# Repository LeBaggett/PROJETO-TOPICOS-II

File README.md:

# Videogame Portátil com STM32F103 (Blue Pill)

## Sumário
- [1. Introdução](#1-introdução)
- [2. Objetivos do Projeto](#2-objetivos-do-projeto)
  - [2.1 Objetivo Geral](#21-objetivo-geral)
  - [2.2 Objetivos Específicos](#22-objetivos-específicos)
- [3. Visão Geral do Sistema](#3-visão-geral-do-sistema)
  - [3.1 Arquitetura Geral](#31-arquitetura-geral)
  - [3.2 Fluxo Geral de Operação](#32-fluxo-geral-de-operação)
- [4. Escolha dos Componentes](#4-escolha-dos-componentes)
  - [4.1 Microcontrolador – STM32F103C8T6 (Blue Pill)](#41-microcontrolador--stm32f103c8t6-blue-pill)
  - [4.2 Display – Nokia 5110 (PCD8544)](#42-display--nokia-5110-pcd8544)
  - [4.3 Armazenamento – Cartão SD (Modo SPI)](#43-armazenamento--cartão-sd-modo-spi)
  - [4.4 Interface de Entrada – Botões Táteis](#44-interface-de-entrada--botões-táteis)
  - [4.5 Áudio – Buzzer Passivo](#45-áudio--buzzer-passivo)
- [5. Projeto do Esquemático](#5-projeto-do-esquemático)
  - [5.1 Circuito de Alimentação](#51-circuito-de-alimentação)
  - [5.2 Desacoplamento do Microcontrolador e Periféricos](#52-desacoplamento-do-microcontrolador-e-periféricos)
  - [5.3 Comunicação SPI](#53-comunicação-spi)
  - [5.4 Interface com o Display](#54-interface-com-o-display)
  - [5.5 Interface com o Cartão SD](#55-interface-com-o-cartão-sd)
  - [5.6 Interface de Entrada (Botões)](#56-interface-de-entrada-botões)
  - [5.7 Circuito de Áudio](#57-circuito-de-áudio)
- [6. Definição de Pinout](#6-definição-de-pinout)
  - [6.1 Tabela de Pinout](#61-tabela-de-pinout)
  - [6.2 Justificativa do Pinout](#62-justificativa-do-pinout)
- [7. Projeto da PCB](#7-projeto-da-pcb)
  - [7.1 Considerações Gerais](#71-considerações-gerais)
  - [7.2 Primeira Versão da PCB](#72-primeira-versão-da-pcb)
  - [7.3 Segunda Versão da PCB](#73-segunda-versão-da-pcb)
  - [7.4 Análise do Layout Final](#74-análise-do-layout-final)
- [8. Visualização 3D e Montagem](#8-visualização-3d-e-montagem)
  - [8.1 Modelo 3D da PCB](#81-modelo-3d-da-pcb)
  - [8.2 Considerações de Montagem](#82-considerações-de-montagem)
- [9. Conclusão](#9-conclusão)
- [10. Referências](#10-referências)

---

## 1. Introdução
Este documento apresenta a **documentação técnica do hardware** de um videogame portátil desenvolvido com foco educacional e experimental, baseado no microcontrolador **STM32F103C8T6 (Blue Pill)**. O objetivo principal desta documentação é **descrever, justificar e analisar as decisões de projeto de hardware**, desde a escolha dos componentes até o esquemático elétrico e o layout final da PCB.

O projeto foi concebido para integrar conceitos de eletrônica digital, sistemas embarcados e boas práticas de projeto de placas de circuito impresso, priorizando simplicidade, modularidade e confiabilidade elétrica. Questões relacionadas a firmware são abordadas apenas quando necessárias para justificar decisões de hardware.

---

## 2. Objetivos do Projeto

### 2.1 Objetivo Geral
Desenvolver e documentar o **hardware de um videogame portátil**, incluindo esquemático elétrico e PCB, utilizando componentes amplamente disponíveis e de baixo custo, garantindo funcionamento estável e possibilidade de expansão futura.

### 2.2 Objetivos Específicos
- Selecionar um microcontrolador adequado para aplicações gráficas simples e controle de periféricos  
- Projetar um circuito de alimentação estável em 3,3 V  
- Implementar comunicação SPI confiável para display gráfico e cartão SD  
- Desenvolver uma interface física com botões e sinalização sonora  
- Aplicar boas práticas de desacoplamento, filtragem e layout de PCB  

---

## 3. Visão Geral do Sistema

### 3.1 Arquitetura Geral
O sistema é composto pelos seguintes blocos funcionais:
- Unidade de processamento baseada no STM32F103  
- Interface de usuário composta por display gráfico, botões e buzzer  
- Sistema de armazenamento removível via cartão SD  
- Circuito de alimentação em 3,3 V  

### 3.2 Fluxo Geral de Operação
1. Energização do circuito e estabilização da alimentação  
2. Inicialização do microcontrolador  
3. Configuração dos periféricos SPI  
4. Leitura das entradas do usuário  
5. Atualização do display e geração de áudio  

---

## 4. Escolha dos Componentes

### 4.1 Microcontrolador – STM32F103C8T6 (Blue Pill)
<div align="center">
<br><figure align="center">
  <div> 

  </div>
</figure><br>
<div align="center">
  <figcaption>
    <b>Figura 1</b> – Microcontrolador STM32F103C8T6 e sua Dev Board (Blue Pill)
  </figcaption>
</div><br>
</div>

O STM32F103C8T6 foi escolhido por oferecer um equilíbrio adequado entre desempenho, custo e disponibilidade. O núcleo ARM Cortex-M3 operando a até 72 MHz é suficiente para aplicações gráficas simples, leitura de entradas e controle de periféricos.

A utilização do módulo Blue Pill reduz a complexidade do projeto, facilita testes e depuração e permite foco no desenvolvimento do restante do hardware.

## Visão Geral

A família **STM32F103xx de média densidade da linha performance** incorpora o núcleo **Arm® Cortex®-M3 de 32 bits**, de alto desempenho, operando a uma frequência de até **72 MHz**, memórias embarcadas de alta velocidade (**Flash de até 128 Kbytes** e **SRAM de até 20 Kbytes**), além de uma ampla variedade de **E/S aprimoradas** e **periféricos** conectados a dois barramentos **APB**.

Todos os dispositivos oferecem **dois ADCs de 12 bits**, **três temporizadores de uso geral de 16 bits** mais **um temporizador PWM**, bem como interfaces de comunicação padrão e avançadas: até **dois I2Cs e SPIs**, **três USARTs**, **USB** e **CAN**.

Os dispositivos operam com alimentação de **2,0 a 3,6 V**. Estão disponíveis tanto na faixa de temperatura de **–40 a +85 °C** quanto na faixa estendida de **–40 a +105 °C**. Um conjunto abrangente de **modos de economia de energia** permite o projeto de aplicações de baixo consumo.

A família STM32F103xx de média densidade inclui dispositivos em **seis tipos diferentes de encapsulamento**, variando de **36 pinos a 100 pinos**. Dependendo do dispositivo escolhido, diferentes conjuntos de periféricos são incluídos. A descrição a seguir fornece uma visão geral da gama completa de periféricos oferecidos por esta família.

Essas características tornam a família de microcontroladores STM32F103xx de média densidade adequada para uma ampla gama de aplicações, como **acionamento de motores**, **controle de aplicações**, **equipamentos médicos e portáteis**, **periféricos para PC e jogos**, **plataformas GPS**, **aplicações industriais**, **CLPs**, **inversores**, **impressoras**, **scanners**, **sistemas de alarme**, **interfones de vídeo** e **sistemas HVAC**.

---

## Características

### Núcleo
- Núcleo **Arm® Cortex®-M3 de 32 bits**
- Frequência máxima de **72 MHz**
- Desempenho de **1,25 DMIPS/MHz** (Dhrystone 2.1) com acesso à memória sem wait states
- Multiplicação em ciclo único e divisão por hardware

### Memórias
- **64 ou 128 Kbytes** de memória Flash
- **20 Kbytes** de SRAM

### Gerenciamento de clock, reset e alimentação
- Alimentação da aplicação e E/S de **2,0 a 3,6 V**
- **POR**, **PDR** e detector de tensão programável (**PVD**)
- Oscilador a cristal de **4 a 16 MHz**
- Oscilador RC interno de **8 MHz** calibrado em fábrica
- Oscilador RC interno de **40 kHz**
- **PLL** para clock da CPU
- Oscilador de **32 kHz** para RTC com calibração

### Baixo consumo
- Modos **Sleep**, **Stop** e **Standby**
- Alimentação **VBAT** para RTC e registradores de backup

### Conversores A/D
- **2 conversores A/D de 12 bits**, **1 µs** (até **16 canais**)
- Faixa de conversão: **0 a 3,6 V**
- Capacidade de **dupla amostragem e retenção**
- **Sensor de temperatura** interno

### DMA
- Controlador DMA de **7 canais**
- Periféricos suportados: temporizadores, ADC, SPI, I2C e USART

### Portas de E/S
- Até **80 portas de E/S rápidas**
- **26 / 37 / 51 / 80 E/S**, todas mapeáveis em **16 vetores de interrupção externa** e quase todas **tolerantes a 5 V**

### Depuração
- Interfaces de depuração **Serial Wire Debug (SWD)** e **JTAG**

### Temporizadores
- **Três temporizadores de 16 bits**, cada um com até 4 canais IC/OC/PWM ou contador de pulsos e entrada de encoder incremental (quadratura)
- Temporizador PWM de **16 bits para controle de motores**, com geração de dead-time e parada de emergência
- **Dois watchdogs** (independente e de janela)
- Temporizador **SysTick** de 24 bits (contador regressivo)

### Interfaces de comunicação
- Até **nove interfaces de comunicação**
- Até **duas interfaces I2C** (SMBus/PMBus®)
- Até **três USARTs** (interface ISO 7816, LIN, capacidade IrDA, controle de modem)
- Até **duas interfaces SPI** (até **18 Mbit/s**)
- Interface **CAN 2.0B Active**
- Interface **USB 2.0 Full-Speed**

### Outros recursos
- Unidade de cálculo **CRC**
- **ID único de 96 bits**
- Encapsulamentos **ECOPACK®**

### 4.2 Display – Nokia 5110 (PCD8544)

<br><div align="center">
  <figure>
      
  </figure><br>
</div><br>

<div align="center">
  <figcaption>
    <b>Figura 2</b> – Display LCD Nokia 5110
  </figcaption>
</div><br>

O display Nokia 5110 foi selecionado por sua simplicidade de interface, baixo consumo de energia e ampla documentação disponível. Sua resolução de 84x48 pixels é adequada para jogos 2D simples e menus gráficos.

### 4.3 Armazenamento – Cartão SD (Modo SPI)

<br><div align="center">
  <figure>
      
  </figure><br>
</div><br>

<div align="center">
  <figcaption>
    <b>Figura 3</b> – Módulo Micro Cartão SD
  </figcaption>
</div><br>

O cartão SD operando em modo SPI oferece alta capacidade de armazenamento com baixa complexidade de hardware. Ele é utilizado para armazenamento de dados persistentes como estados de jogos e configurações.

### 4.4 Interface de Entrada – Botões Táteis
Os botões táteis foram escolhidos por sua robustez, simplicidade elétrica e fácil integração com GPIOs do microcontrolador. O tratamento de debounce é realizado via software.

### 4.5 Áudio – Buzzer Passivo
O buzzer passivo permite geração de áudio por PWM, utilizando timers internos do STM32. Essa abordagem oferece flexibilidade sonora com baixo custo e simplicidade de hardware.

---

## 5. Projeto do Esquemático

O esquemático elétrico do videogame portátil foi desenvolvido com foco em simplicidade, robustez elétrica e boas práticas de projeto para sistemas embarcados. A organização do circuito segue uma divisão funcional clara, permitindo fácil compreensão, manutenção e futuras modificações.

<div align="center">
<figure align="center">
  
  <figcaption>
    <b>Figura 4</b> – Esquemático elétrico versão v1
  </figcaption>
</figure>
</div><br>

<p align="center">
  <a href="hardware/ProtoGame/ProtoGame-jobset-file/ProtoGame-schematic-v1/ProtoGame.pdf">Esquemático elétrico completo (PDF)</a>
</p><br>

---

### 5.1 Circuito de Alimentação

O sistema foi projetado para operar integralmente em **3,3 V**, tensão compatível com o microcontrolador STM32F103C8T6 e com todos os periféricos utilizados. A alimentação principal é fornecida por uma bateria, cuja tensão é regulada por um regulador linear **AMS1117-3.3**.

O regulador AMS1117 foi escolhido por sua ampla disponibilidade e facilidade de aplicação, sendo adequado para projetos educacionais e protótipos funcionais. Apesar de sua eficiência inferior quando comparado a reguladores chaveados, seu uso é justificado pelo consumo moderado do sistema e pela simplicidade do circuito.

Na entrada e na saída do regulador são utilizados capacitores de filtragem, conforme recomendado pelo fabricante, garantindo estabilidade da tensão e evitando oscilações indesejadas.

---

### 5.2 Capacitores Bulk e Filtragem de Baixa Frequência

O capacitor **bulk** de maior valor (47 µF) foi inserido na linha de alimentação principal com o objetivo de absorver variações lentas de corrente e fornecer energia instantânea durante picos de consumo, especialmente durante inicialização do sistema e acesso ao cartão SD.

Além do capacitor bulk principal, capacitores adicionais de **4,7 µF** são distribuídos próximos a blocos específicos do circuito, atuando como suporte local de energia. Essa abordagem reduz quedas momentâneas de tensão e melhora a estabilidade global da alimentação.

O uso combinado de capacitores de diferentes valores cria um efeito de filtragem em larga faixa de frequência, aumentando a confiabilidade do sistema.

---

### 5.3 Desacoplamento do Microcontrolador e Periféricos

Cada circuito integrado presente no projeto possui capacitores cerâmicos de **100 nF** posicionados o mais próximo possível de seus pinos de alimentação. Esses capacitores atuam como desacoplamento de alta frequência, reduzindo ruídos gerados por comutações internas e interferências no barramento de alimentação.

O microcontrolador STM32F103C8T6 possui múltiplos pinos de alimentação (VDD e VDDA), sendo essencial o desacoplamento individual de cada domínio. O domínio analógico (VDDA) recebe atenção especial, garantindo menor interferência em funções sensíveis internas do microcontrolador.

Essa prática evita resets espúrios, falhas de comunicação SPI e comportamentos instáveis durante operação contínua.

---

### 5.4 Comunicação SPI

A comunicação SPI é utilizada para interface com o display gráfico Nokia 5110 e com o módulo de cartão SD. Ambos os dispositivos compartilham as linhas de clock (SCK) e dados (MOSI e MISO), utilizando sinais de **Chip Select independentes** para controle de acesso.

Foram adicionados resistores em série nas linhas de clock e dados, próximos ao microcontrolador, com a finalidade de reduzir efeitos de ringing, overshoot e reflexões em trilhas mais longas. Essa técnica melhora significativamente a integridade do sinal, especialmente no acesso ao cartão SD, que é mais sensível a ruídos.

Resistores de pull-up nos sinais de Chip Select garantem que os dispositivos permaneçam desabilitados durante a inicialização do sistema.

---

### 5.5 Interface com o Display LCD

O display Nokia 5110 utiliza o barramento SPI para comunicação de dados e comandos, além de sinais adicionais de controle como **Reset** e **Data/Command**. Esses sinais são controlados diretamente por GPIOs do microcontrolador.

A alimentação do display é feita em 3,3 V, eliminando a necessidade de conversores de nível lógico. O controle do backlight é realizado por meio de um pino dedicado, permitindo economia de energia quando o display não está em uso.

A escolha desse display contribui para um circuito simples, de baixo consumo e fácil integração.

---

### 5.6 Interface com o Cartão SD

O cartão SD é operado em **modo SPI**, reduzindo significativamente a complexidade do hardware quando comparado ao modo SD nativo. Essa abordagem é suficiente para leitura e escrita de dados de pequeno volume, como estados de jogos e configurações.

Capacitores de desacoplamento dedicados são utilizados próximos ao módulo SD, devido aos picos de corrente característicos durante operações de escrita. Essa decisão é fundamental para evitar falhas intermitentes de comunicação.

---

### 5.7 Interface de Entrada – Botões

Os botões táteis são conectados diretamente aos pinos GPIO do microcontrolador, utilizando resistores de polarização de **10 kΩ** para garantir níveis lógicos definidos quando não acionados. Essa configuração evita estados flutuantes e simplifica o circuito.

O tratamento de debounce é realizado via software, reduzindo a quantidade de componentes externos e mantendo o esquemático mais enxuto.

---

### 5.8 Circuito de Áudio

O circuito de áudio é composto por um buzzer passivo acionado por um pino de timer do STM32F103, permitindo geração de sinais PWM em diferentes frequências. Essa abordagem possibilita a criação de efeitos sonoros simples, adequados para um videogame portátil.

A escolha do buzzer passivo oferece maior flexibilidade sonora em comparação a buzzers ativos, mantendo baixo custo e simplicidade de implementação.

---

## 6. Bill of Materials (BoM)

A Bill of Materials apresenta todos os componentes utilizados no projeto, sendo essencial para reprodução do hardware, aquisição de peças e validação do circuito.

<div align="center">

**Tabela 2** – Bill of Materials (BoM).

| Referência | Qtd | Valor / Modelo | Função |
|:----------|:---:|----------------|--------|
| BT1 | 1 | Battery | Alimentação do sistema |
| BZ1 | 1 | Buzzer | Saída de áudio |
| C1–C2, C4–C6, C9 | 6 | 100 nF | Desacoplamento |
| C3 | 1 | 47 µF | Capacitor bulk |
| C7–C8 | 2 | 4.7 µF | Filtragem local |
| J1 | 1 | SD Card Module | Armazenamento |
| LCD_Nokia1 | 1 | Nokia 5110 | Display gráfico |
| R1–R11 | 11 | 10 kΩ | Pull-up / Pull-down |
| SW1 | 1 | SW_DPST_x2 | Chave geral |
| SW2–SW10 | 9 | SW_MEC_5E | Botões |
| U1 | 1 | STM32F103C8T6 | Microcontrolador |
| U2 | 1 | AMS1117-3.3 | Regulador 3,3 V |

</div>

---

## 6. Definição de Pinout

<br><div align="center">
  <figure>
      
  </figure><br>
</div><br>

<div align="center">
  <figcaption>
    <b>Figura 5</b> – IOC MCU Pinout
  </figcaption>
</div><br>

### 6.1 Tabela de Pinout

<br><div align="center">

**Tabela 1** – Mapeamento de pinos do STM32F103C8T6.
  
| Pino | Nome (MCU) | Função |
|:-----:|:------------:|:--------|
| 1 | VBAT | Alimentação de bateria |
| 5 | PD0 | Cristal externo (OSC_IN) |
| 6 | PD1 | Cristal externo (OSC_OUT) |
| 7 | NRST | Reset |
| 10 | PA0 | Reset do LCD |
| 11 | PA1 | LCD Data/Command |
| 13 | PA3 | CS do LCD |
| 14 | PA4 | CS do Cartão SD |
| 15 | PA5 | SPI1 SCK |
| 16 | PA6 | SPI1 MISO |
| 17 | PA7 | SPI1 MOSI |
| 18 | PB0 | Backlight do LCD |
| 29 | PA8 | Buzzer |
| 30–42 | PA9–PB6 | Botões |
| 34 | PA13 | SWDIO |
| 37 | PA14 | SWCLK |
| 44 | BOOT0 | Seleção de boot |

</div><br>

### 6.2 Justificativa do Pinout
O pinout foi definido priorizando o uso do SPI1, timers dedicados para PWM e pinos compatíveis com depuração SWD, garantindo organização e facilidade de manutenção.

---

## 7. Projeto da PCB

### 7.1 Considerações Iniciais e Restrições de Fabricação

O projeto da placa de circuito impresso (PCB) do videogame portátil foi desenvolvido considerando, desde o início, as **restrições reais de fabricação impostas pelo processo de fresagem CNC**, disponível no **Laboratório de Engenharia de Sistemas Computacionais (LESC) da Universidade Federal do Ceará (UFC)**.

Diferentemente de processos industriais convencionais (como fabricação química com máscara de solda e acabamento superficial), a fresagem CNC impõe limitações específicas, tais como:
- Ausência de máscara de solda  
- Trilhas e espaçamentos maiores  
- Vias de maior diâmetro  
- Cobre exposto (sem HASL ou ENIG)  

Essas restrições influenciaram diretamente as decisões de layout, regras de projeto e escolha de encapsulamentos, priorizando **robustez mecânica, confiabilidade elétrica e facilidade de montagem manual**.

### 7.2 Definição do Stackup da PCB

<div align="center">
<br><figure align="center">
  <div> 

  </div>
</figure><br>
<div align="center">
  <figcaption>
    <b>Figura 6</b> – Camadas Top e Bottom da PCB
  </figcaption>
</div><br>
</div>

A placa foi projetada com **duas camadas condutoras (Top e Bottom)**, configuração que representa um compromisso adequado entre custo, complexidade e desempenho elétrico para a aplicação proposta.

A escolha por duas camadas foi motivada pelos seguintes fatores:
- Frequências de operação relativamente baixas (SPI e GPIO)  
- Ausência de circuitos analógicos sensíveis ou RF  
- Possibilidade de implementação de planos de referência contínuos  
- Compatibilidade com o processo de fabricação por CNC  

Essa configuração é suficiente para garantir bom retorno de corrente, roteamento organizado e estabilidade elétrica, sem a complexidade adicional de PCBs multicamadas.

### 7.3 Regras de Projeto e Parâmetros de Fabricação

As regras de projeto foram definidas explicitamente no KiCad, levando em consideração as capacidades da fresadora CNC disponível no laboratório.

As principais regras adotadas foram:
- **Largura mínima de trilha:** 0,5 mm  
- **Diâmetro mínimo de furo de via:** 0,9 mm  
- **Diâmetro do pad da via:** 1,5 mm  
- **Espaçamento entre trilhas:** padrão do KiCad  

Esses valores garantem:
- Boa taxa de sucesso na fabricação  
- Facilidade de soldagem manual  
- Redução de falhas por descontinuidade de trilhas  

A espessura da placa foi mantida como o **valor padrão do KiCad**, compatível com laminados FR4 comumente utilizados em ambientes acadêmicos.

### 7.4 Estratégia de Aterramento (GND)

O aterramento do sistema foi implementado por meio de **planos de GND contínuos em ambas as camadas da PCB**, cobrindo praticamente toda a área da placa.

Essa abordagem proporciona:
- Caminhos de retorno de corrente de baixa impedância  
- Redução de ruído eletromagnético  
- Maior estabilidade para o barramento SPI  
- Melhor comportamento do sistema de alimentação  

Não foram utilizadas **vias de costura (stitching vias)** dedicadas exclusivamente ao aterramento. Apenas vias funcionais foram empregadas, conectando o plano de GND entre as camadas quando necessário. Essa decisão simplificou o processo de fabricação e montagem, sendo considerada adequada para as frequências e correntes envolvidas no projeto.

### 7.5 Distribuição de Alimentação e Desacoplamento

Todo o sistema opera em **3,3 V**, tensão compatível com o microcontrolador STM32F103, o display gráfico e o cartão SD. A utilização de uma única tensão de alimentação reduz a complexidade do circuito e elimina a necessidade de conversores de nível lógico.

#### 7.5.1 Capacitores de Desacoplamento
Foram utilizados capacitores cerâmicos de **100 nF**, posicionados o mais próximo possível dos pinos de alimentação do microcontrolador e dos periféricos. Essa prática minimiza a indutância parasita e melhora a resposta a transientes de corrente.

#### 7.5.2 Capacitor Bulk
Um capacitor eletrolítico de **47 µF** foi posicionado próximo ao microcontrolador, atuando como capacitor de bulk para absorver variações mais lentas de corrente e estabilizar a tensão do barramento de alimentação.

#### 7.5.3 Alimentação do Cartão SD e do Display
Tanto o módulo de cartão SD quanto o display gráfico possuem **capacitores dedicados de desacoplamento**, além de estarem conectados ao barramento principal de 3,3 V. Essa decisão considera os picos de corrente característicos do cartão SD durante operações de leitura e escrita.

O dimensionamento dos capacitores seguiu valores amplamente utilizados em aplicações similares, sendo suficiente para garantir funcionamento estável, mesmo sem cálculo analítico detalhado.

### 7.6 Roteamento do Barramento SPI

O barramento SPI é utilizado para comunicação com o display gráfico e com o cartão SD. O roteamento foi realizado buscando:
- Trilhas relativamente curtas  
- Pouca utilização de vias  
- Organização vertical das conexões

<div align="center">
<br><figure align="center">
  <div> 

  </div>
</figure><br>
<div align="center">
  <figcaption>
    <b>Figura 7</b> – Roteamento nas camadas Top e Bottom da PCB
  </figcaption>
</div><br>
</div> 

Considerando as dimensões da placa, a maior distância entre dispositivos no barramento SPI é da ordem de **50 mm**, valor adequado para as frequências utilizadas no projeto.

No esquemático, foram previstos **resistores em série** nas linhas:
- SCK: 33 Ω  
- MOSI: 22 Ω  

Entretanto, esses resistores não foram implementados na versão final do layout da PCB. Por outro lado, foram utilizados **resistores de pull-up de 10 kΩ nas linhas de Chip Select**, garantindo que os dispositivos SPI permaneçam desabilitados durante a inicialização do sistema.

### 7.7 Clock do Microcontrolador

O projeto utiliza o **módulo Blue Pill**, que já incorpora um cristal externo (8 MHz ou 16 MHz, dependendo da versão), bem como os capacitores de carga necessários.

Essa escolha elimina a necessidade de roteamento de sinais de clock sensíveis na PCB principal, reduzindo riscos de ruído, erros de temporização e falhas de oscilação, além de simplificar o layout.

### 7.8 Considerações Mecânicas e Ergonomia

A disposição dos componentes na PCB levou em conta simultaneamente:
- **Ergonomia do usuário**  
- **Simetria visual**  
- **Facilidade de roteamento**  

Os botões foram posicionados de forma a permitir operação confortável com os polegares, enquanto o display foi centralizado mecanicamente, considerando sua espessura e o uso de espaçadores.

Foram utilizados **furos de montagem com diâmetro de 3,2 mm**, compatíveis com parafusos M3, permitindo a fixação segura da placa em um eventual gabinete.

### 7.9 Evolução do Projeto: PCB V0 para PCB V1

A transição da versão inicial da PCB (V0) para a versão revisada (V1) foi motivada por múltiplos fatores:
- Correção de erros elétricos  
- Ajustes mecânicos  
- Melhor distribuição dos componentes  
- Melhoria estética do conjunto  
- Facilidade de fabricação e montagem  

Durante esse processo, foi identificado um **erro dimensional em um footprint**, que resultava em interferência mecânica durante a montagem. Esse problema foi corrigido na versão V1, reforçando a importância de validações mecânicas e revisões iterativas no projeto de PCBs.

### 7.10 Limitações Assumidas do Layout

Algumas limitações foram conscientemente aceitas no projeto, tais como:
- Ausência de máscara de solda  
- Não utilização de vias de costura de GND  
- Resistores série do SPI não implementados no layout  

Essas decisões são justificadas pelo contexto acadêmico, pelas restrições de fabricação por CNC e pelos requisitos elétricos relativamente modestos do sistema.

---

## 8. Visualização 3D e Montagem

### 8.1 Modelo 3D da PCB
Modelos 3D foram gerados no KiCad para validação mecânica e visual.

<div align="center">
<br><figure align="center">
  <div> 

  </div>
</figure><br>
<div align="center">
  <figcaption>
    <b>Figura 8</b> – Top e Bottom do Modelo 3D da PCB
  </figcaption>
</div><br>
</div> 

### 8.2 Considerações de Montagem
O posicionamento dos componentes facilita acesso ao display, botões e cartão SD.

<div align="center">
<br><figure align="center">
  <div> 

  </div>
</figure><br>
<div align="center">
  <figcaption>
    <b>Figura 7</b> – Top e Bottom da PCB
  </figcaption>
</div><br>
</div>

---

## 9. Conclusão
O projeto atinge os objetivos propostos, resultando em um hardware funcional, organizado e adequado para fins educacionais e experimentais.

---

## 10. Referências
- Datasheets: <a href="documentação/Datasheets">Datasheets consultados</a>  
- Application Notes da STMicroelectronics  
- KiCad Documentation

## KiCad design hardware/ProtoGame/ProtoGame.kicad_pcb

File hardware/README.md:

# Videogame Portátil com STM32F103 (Blue Pill)

## Sumário
- [1. Introdução](#1-introdução)
- [2. Objetivos do Projeto](#2-objetivos-do-projeto)
  - [2.1 Objetivo Geral](#21-objetivo-geral)
  - [2.2 Objetivos Específicos](#22-objetivos-específicos)
- [3. Visão Geral do Sistema](#3-visão-geral-do-sistema)
  - [3.1 Arquitetura Geral](#31-arquitetura-geral)
  - [3.2 Fluxo Geral de Operação](#32-fluxo-geral-de-operação)
- [4. Escolha dos Componentes](#4-escolha-dos-componentes)
  - [4.1 Microcontrolador – STM32F103C8T6 (Blue Pill)](#41-microcontrolador--stm32f103c8t6-blue-pill)
  - [4.2 Display – Nokia 5110 (PCD8544)](#42-display--nokia-5110-pcd8544)
  - [4.3 Armazenamento – Cartão SD (Modo SPI)](#43-armazenamento--cartão-sd-modo-spi)
  - [4.4 Interface de Entrada – Botões Táteis](#44-interface-de-entrada--botões-táteis)
  - [4.5 Áudio – Buzzer Passivo](#45-áudio--buzzer-passivo)
- [5. Projeto do Esquemático](#5-projeto-do-esquemático)
  - [5.1 Circuito de Alimentação](#51-circuito-de-alimentação)
  - [5.2 Desacoplamento do Microcontrolador e Periféricos](#52-desacoplamento-do-microcontrolador-e-periféricos)
  - [5.3 Comunicação SPI](#53-comunicação-spi)
  - [5.4 Interface com o Display](#54-interface-com-o-display)
  - [5.5 Interface com o Cartão SD](#55-interface-com-o-cartão-sd)
  - [5.6 Interface de Entrada (Botões)](#56-interface-de-entrada-botões)
  - [5.7 Circuito de Áudio](#57-circuito-de-áudio)
- [6. Definição de Pinout](#6-definição-de-pinout)
  - [6.1 Tabela de Pinout](#61-tabela-de-pinout)
  - [6.2 Justificativa do Pinout](#62-justificativa-do-pinout)
- [7. Projeto da PCB](#7-projeto-da-pcb)
  - [7.1 Considerações Gerais](#71-considerações-gerais)
  - [7.2 Primeira Versão da PCB](#72-primeira-versão-da-pcb)
  - [7.3 Segunda Versão da PCB](#73-segunda-versão-da-pcb)
  - [7.4 Análise do Layout Final](#74-análise-do-layout-final)
- [8. Visualização 3D e Montagem](#8-visualização-3d-e-montagem)
  - [8.1 Modelo 3D da PCB](#81-modelo-3d-da-pcb)
  - [8.2 Considerações de Montagem](#82-considerações-de-montagem)
- [9. Conclusão](#9-conclusão)
- [10. Referências](#10-referências)

---

## 1. Introdução
Este documento apresenta a **documentação técnica do hardware** de um videogame portátil desenvolvido com foco educacional e experimental, baseado no microcontrolador **STM32F103C8T6 (Blue Pill)**. O objetivo principal desta documentação é **descrever, justificar e analisar as decisões de projeto de hardware**, desde a escolha dos componentes até o esquemático elétrico e o layout final da PCB.

O projeto foi concebido para integrar conceitos de eletrônica digital, sistemas embarcados e boas práticas de projeto de placas de circuito impresso, priorizando simplicidade, modularidade e confiabilidade elétrica. Questões relacionadas a firmware são abordadas apenas quando necessárias para justificar decisões de hardware.

---

## 2. Objetivos do Projeto

### 2.1 Objetivo Geral
Desenvolver e documentar o **hardware de um videogame portátil**, incluindo esquemático elétrico e PCB, utilizando componentes amplamente disponíveis e de baixo custo, garantindo funcionamento estável e possibilidade de expansão futura.

### 2.2 Objetivos Específicos
- Selecionar um microcontrolador adequado para aplicações gráficas simples e controle de periféricos  
- Projetar um circuito de alimentação estável em 3,3 V  
- Implementar comunicação SPI confiável para display gráfico e cartão SD  
- Desenvolver uma interface física com botões e sinalização sonora  
- Aplicar boas práticas de desacoplamento, filtragem e layout de PCB  

---

## 3. Visão Geral do Sistema

### 3.1 Arquitetura Geral
O sistema é composto pelos seguintes blocos funcionais:
- Unidade de processamento baseada no STM32F103  
- Interface de usuário composta por display gráfico, botões e buzzer  
- Sistema de armazenamento removível via cartão SD  
- Circuito de alimentação em 3,3 V  

### 3.2 Fluxo Geral de Operação
1. Energização do circuito e estabilização da alimentação  
2. Inicialização do microcontrolador  
3. Configuração dos periféricos SPI  
4. Leitura das entradas do usuário  
5. Atualização do display e geração de áudio  

---

## 4. Escolha dos Componentes

### 4.1 Microcontrolador – STM32F103C8T6 (Blue Pill)
<div align="center">
<br><figure align="center">
  <div> 

  </div>
</figure><br>
<div align="center">
  <figcaption>
    <b>Figura 1</b> – Microcontrolador STM32F103C8T6 e sua Dev Board (Blue Pill)
  </figcaption>
</div><br>
</div>

O STM32F103C8T6 foi escolhido por oferecer um equilíbrio adequado entre desempenho, custo e disponibilidade. O núcleo ARM Cortex-M3 operando a até 72 MHz é suficiente para aplicações gráficas simples, leitura de entradas e controle de periféricos.

A utilização do módulo Blue Pill reduz a complexidade do projeto, facilita testes e depuração e permite foco no desenvolvimento do restante do hardware.

### 4.2 Display – Nokia 5110 (PCD8544)

<br><div align="center">
  <figure>
      
  </figure><br>
</div><br>

<div align="center">
  <figcaption>
    <b>Figura 2</b> – Display LCD Nokia 5110
  </figcaption>
</div><br>

O display Nokia 5110 foi selecionado por sua simplicidade de interface, baixo consumo de energia e ampla documentação disponível. Sua resolução de 84x48 pixels é adequada para jogos 2D simples e menus gráficos.

### 4.3 Armazenamento – Cartão SD (Modo SPI)

<br><div align="center">
  <figure>
      
  </figure><br>
</div><br>

<div align="center">
  <figcaption>
    <b>Figura 3</b> – Módulo Micro Cartão SD
  </figcaption>
</div><br>

O cartão SD operando em modo SPI oferece alta capacidade de armazenamento com baixa complexidade de hardware. Ele é utilizado para armazenamento de dados persistentes como estados de jogos e configurações.

### 4.4 Interface de Entrada – Botões Táteis
Os botões táteis foram escolhidos por sua robustez, simplicidade elétrica e fácil integração com GPIOs do microcontrolador. O tratamento de debounce é realizado via software.

### 4.5 Áudio – Buzzer Passivo
O buzzer passivo permite geração de áudio por PWM, utilizando timers internos do STM32. Essa abordagem oferece flexibilidade sonora com baixo custo e simplicidade de hardware.

---

## 5. Projeto do Esquemático

O esquemático elétrico do videogame portátil foi desenvolvido com foco em simplicidade, robustez elétrica e boas práticas de projeto para sistemas embarcados. A organização do circuito segue uma divisão funcional clara, permitindo fácil compreensão, manutenção e futuras modificações.

<figure align="center">
  
  <figcaption>
    <b>Figura 4</b> – Esquemático elétrico versão v1
  </figcaption>
</figure>

<p align="center">
  <a href="ProtoGame/ProtoGame-schematic-v1.pdf">Esquemático elétrico completo (PDF)</a>
</p>

---

### 5.1 Circuito de Alimentação

O sistema foi projetado para operar integralmente em **3,3 V**, tensão compatível com o microcontrolador STM32F103C8T6 e com todos os periféricos utilizados. A alimentação principal é fornecida por uma bateria, cuja tensão é regulada por um regulador linear **AMS1117-3.3**.

O regulador AMS1117 foi escolhido por sua ampla disponibilidade e facilidade de aplicação, sendo adequado para projetos educacionais e protótipos funcionais. Apesar de sua eficiência inferior quando comparado a reguladores chaveados, seu uso é justificado pelo consumo moderado do sistema e pela simplicidade do circuito.

Na entrada e na saída do regulador são utilizados capacitores de filtragem, conforme recomendado pelo fabricante, garantindo estabilidade da tensão e evitando oscilações indesejadas.

---

### 5.2 Capacitores Bulk e Filtragem de Baixa Frequência

O capacitor **bulk** de maior valor (47 µF) foi inserido na linha de alimentação principal com o objetivo de absorver variações lentas de corrente e fornecer energia instantânea durante picos de consumo, especialmente durante inicialização do sistema e acesso ao cartão SD.

Além do capacitor bulk principal, capacitores adicionais de **4,7 µF** são distribuídos próximos a blocos específicos do circuito, atuando como suporte local de energia. Essa abordagem reduz quedas momentâneas de tensão e melhora a estabilidade global da alimentação.

O uso combinado de capacitores de diferentes valores cria um efeito de filtragem em larga faixa de frequência, aumentando a confiabilidade do sistema.

---

### 5.3 Desacoplamento do Microcontrolador e Periféricos

Cada circuito integrado presente no projeto possui capacitores cerâmicos de **100 nF** posicionados o mais próximo possível de seus pinos de alimentação. Esses capacitores atuam como desacoplamento de alta frequência, reduzindo ruídos gerados por comutações internas e interferências no barramento de alimentação.

O microcontrolador STM32F103C8T6 possui múltiplos pinos de alimentação (VDD e VDDA), sendo essencial o desacoplamento individual de cada domínio. O domínio analógico (VDDA) recebe atenção especial, garantindo menor interferência em funções sensíveis internas do microcontrolador.

Essa prática evita resets espúrios, falhas de comunicação SPI e comportamentos instáveis durante operação contínua.

---

### 5.4 Comunicação SPI

A comunicação SPI é utilizada para interface com o display gráfico Nokia 5110 e com o módulo de cartão SD. Ambos os dispositivos compartilham as linhas de clock (SCK) e dados (MOSI e MISO), utilizando sinais de **Chip Select independentes** para controle de acesso.

Foram adicionados resistores em série nas linhas de clock e dados, próximos ao microcontrolador, com a finalidade de reduzir efeitos de ringing, overshoot e reflexões em trilhas mais longas. Essa técnica melhora significativamente a integridade do sinal, especialmente no acesso ao cartão SD, que é mais sensível a ruídos.

Resistores de pull-up nos sinais de Chip Select garantem que os dispositivos permaneçam desabilitados durante a inicialização do sistema.

---

### 5.5 Interface com o Display LCD

O display Nokia 5110 utiliza o barramento SPI para comunicação de dados e comandos, além de sinais adicionais de controle como **Reset** e **Data/Command**. Esses sinais são controlados diretamente por GPIOs do microcontrolador.

A alimentação do display é feita em 3,3 V, eliminando a necessidade de conversores de nível lógico. O controle do backlight é realizado por meio de um pino dedicado, permitindo economia de energia quando o display não está em uso.

A escolha desse display contribui para um circuito simples, de baixo consumo e fácil integração.

---

### 5.6 Interface com o Cartão SD

O cartão SD é operado em **modo SPI**, reduzindo significativamente a complexidade do hardware quando comparado ao modo SD nativo. Essa abordagem é suficiente para leitura e escrita de dados de pequeno volume, como estados de jogos e configurações.

Capacitores de desacoplamento dedicados são utilizados próximos ao módulo SD, devido aos picos de corrente característicos durante operações de escrita. Essa decisão é fundamental para evitar falhas intermitentes de comunicação.

---

### 5.7 Interface de Entrada – Botões

Os botões táteis são conectados diretamente aos pinos GPIO do microcontrolador, utilizando resistores de polarização de **10 kΩ** para garantir níveis lógicos definidos quando não acionados. Essa configuração evita estados flutuantes e simplifica o circuito.

O tratamento de debounce é realizado via software, reduzindo a quantidade de componentes externos e mantendo o esquemático mais enxuto.

---

### 5.8 Circuito de Áudio

O circuito de áudio é composto por um buzzer passivo acionado por um pino de timer do STM32F103, permitindo geração de sinais PWM em diferentes frequências. Essa abordagem possibilita a criação de efeitos sonoros simples, adequados para um videogame portátil.

A escolha do buzzer passivo oferece maior flexibilidade sonora em comparação a buzzers ativos, mantendo baixo custo e simplicidade de implementação.

---

## 6. Bill of Materials (BoM)

A Bill of Materials apresenta todos os componentes utilizados no projeto, sendo essencial para reprodução do hardware, aquisição de peças e validação do circuito.

<div align="center">

**Tabela 2** – Bill of Materials (BoM).

| Referência | Qtd | Valor / Modelo | Função |
|:----------|:---:|----------------|--------|
| BT1 | 1 | Battery | Alimentação do sistema |
| BZ1 | 1 | Buzzer | Saída de áudio |
| C1–C2, C4–C6, C9 | 6 | 100 nF | Desacoplamento |
| C3 | 1 | 47 µF | Capacitor bulk |
| C7–C8 | 2 | 4.7 µF | Filtragem local |
| J1 | 1 | SD Card Module | Armazenamento |
| LCD_Nokia1 | 1 | Nokia 5110 | Display gráfico |
| R1–R11 | 11 | 10 kΩ | Pull-up / Pull-down |
| SW1 | 1 | SW_DPST_x2 | Chave geral |
| SW2–SW10 | 9 | SW_MEC_5E | Botões |
| U1 | 1 | STM32F103C8T6 | Microcontrolador |
| U2 | 1 | AMS1117-3.3 | Regulador 3,3 V |

</div>

---

## 6. Definição de Pinout

<br><div align="center">
  <figure>
      
  </figure><br>
</div><br>

<div align="center">
  <figcaption>
    <b>Figura 5</b> – IOC MCU Pinout
  </figcaption>
</div><br>

### 6.1 Tabela de Pinout

<br><div align="center">

**Tabela 1** – Mapeamento de pinos do STM32F103C8T6.
  
| Pino | Nome (MCU) | Função |
|:-----:|:------------:|:--------|
| 1 | VBAT | Alimentação de bateria |
| 5 | PD0 | Cristal externo (OSC_IN) |
| 6 | PD1 | Cristal externo (OSC_OUT) |
| 7 | NRST | Reset |
| 10 | PA0 | Reset do LCD |
| 11 | PA1 | LCD Data/Command |
| 13 | PA3 | CS do LCD |
| 14 | PA4 | CS do Cartão SD |
| 15 | PA5 | SPI1 SCK |
| 16 | PA6 | SPI1 MISO |
| 17 | PA7 | SPI1 MOSI |
| 18 | PB0 | Backlight do LCD |
| 29 | PA8 | Buzzer |
| 30–42 | PA9–PB6 | Botões |
| 34 | PA13 | SWDIO |
| 37 | PA14 | SWCLK |
| 44 | BOOT0 | Seleção de boot |

</div><br>

### 6.2 Justificativa do Pinout
O pinout foi definido priorizando o uso do SPI1, timers dedicados para PWM e pinos compatíveis com depuração SWD, garantindo organização e facilidade de manutenção.

---

## 7. Projeto da PCB

### 7.1 Considerações Gerais
A PCB foi projetada considerando dimensões compactas, trilhas curtas para SPI e bom plano de terra.

### 7.2 Primeira Versão da PCB
A primeira versão serviu como validação elétrica e identificação de limitações de layout.

### 7.3 Segunda Versão da PCB
A segunda versão incorporou melhorias de roteamento, ergonomia e posicionamento dos componentes.

### 7.4 Análise do Layout Final
O layout final apresenta melhor integridade de sinal, organização visual e facilidade de montagem.

---

## 8. Visualização 3D e Montagem

### 8.1 Modelo 3D da PCB
Modelos 3D foram gerados no KiCad para validação mecânica e visual.

### 8.2 Considerações de Montagem
O posicionamento dos componentes facilita acesso ao display, botões e cartão SD.

---

## 9. Conclusão
O projeto atinge os objetivos propostos, resultando em um hardware funcional, organizado e adequado para fins educacionais e experimentais.

---

## 10. Referências
- Datasheet STM32F103  
- Documentação do display PCD8544  
- Application Notes da STMicroelectronics  
- KiCad Documentation

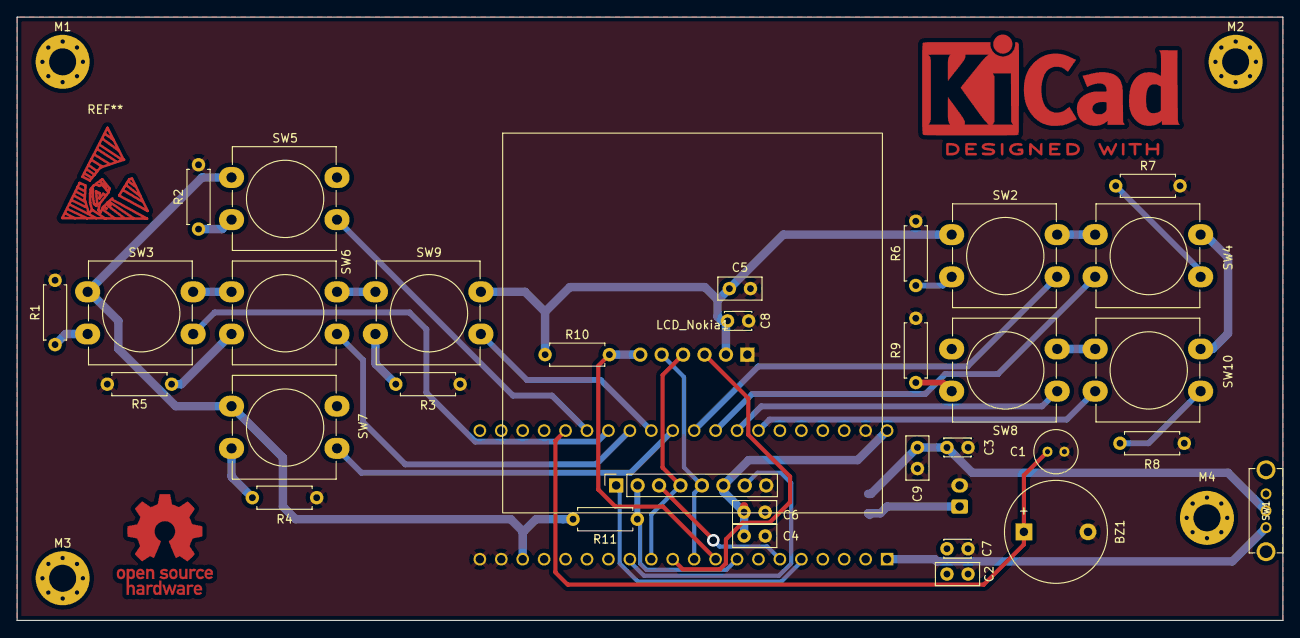
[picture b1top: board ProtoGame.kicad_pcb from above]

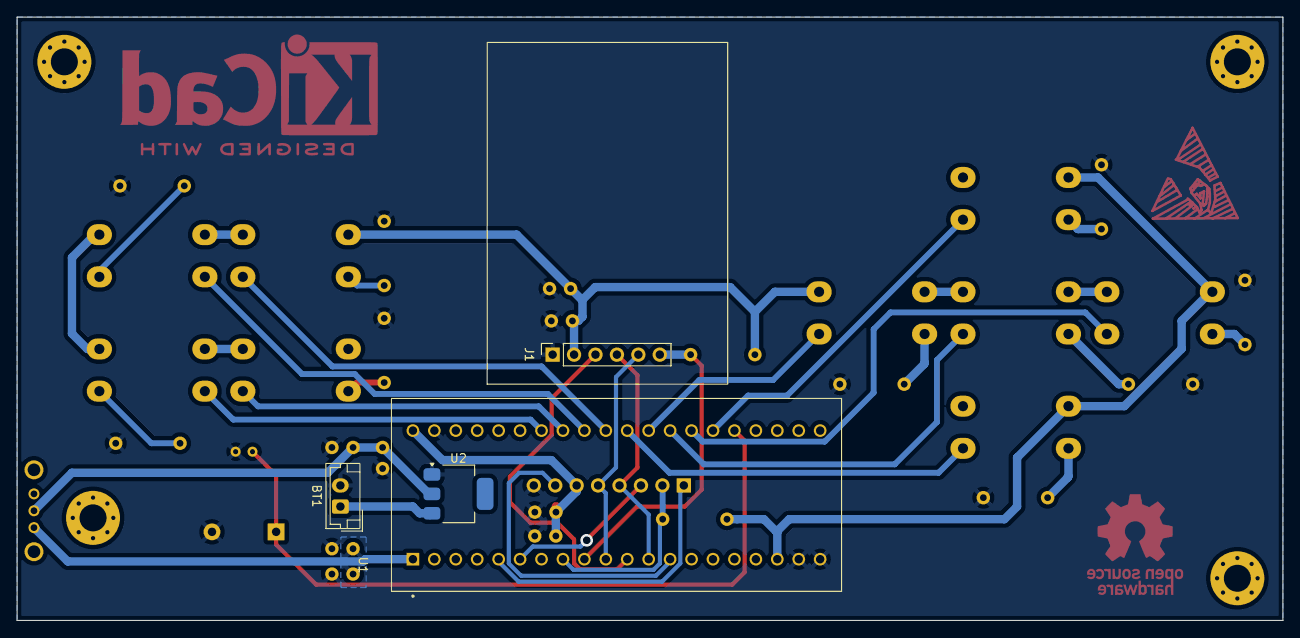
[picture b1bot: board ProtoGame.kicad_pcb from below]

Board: 2 copper layers, 150.0 x 71.5 mm, 40 parts (4 on the bottom side), 32 nets.

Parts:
BT1: Battery_Cell; JST_EH_B2B-EH-A_1x02_P2.50mm_Vertical
BZ1: Buzzer; Buzzer_12x9.5RM7.6
C1: 100nF; C_Radial_D5.0mm_H5.0mm_P2.00mm
C2, C4, C5, C6, C9: 100nF; C_Disc_D5.0mm_W2.5mm_P2.50mm
C3: 47uF; C_Disc_D3.0mm_W2.0mm_P2.50mm
C7, C8: 4.7uF; C_Disc_D3.0mm_W2.0mm_P2.50mm
J1: SD_Card_Module; microsd_module
LCD_Nokia1: 5110; PinSocket_1x08_P2.54mm_Vertical
M1, M2, M3, M4: MountingHole_3.2mm_M3_Pad_Via
R1, R2, R3, R4, R5, R6, R7, R8, R9, R10, R11: 10K; R_Axial_DIN0207_L6.3mm_D2.5mm_P7.62mm_Horizontal
SW1: SW_DPST_x2; SW_EG1213
SW2, SW3, SW4, SW5, SW6, SW7, SW8, SW9, SW10: SW_MEC_5E; SW_PUSH-12mm_Wuerth-430476085716
U1: STM32F103C8Tx - MODULE; MODULE_ZC323000-with-pinholder
U2: AMS1117-3.3; SOT-223-3_TabPin2

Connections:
+3.3V: C4.1, C5.1, C6.1, C8.1, J1.2 (VCC), LCD_Nokia1.6 (VCC), R10.1, R11.2, SW2.1, SW3.1, SW4.1, SW5.1, SW6.1, SW7.1, SW8.1, SW9.1, SW10.1, U1.18 (3.3), U1.40 (3.3)
+3.7V: BT1.1 (+), U2.3 (VI)
B1: SW5.2, U1.26 (A9)
B2: SW3.2, U1.27 (A10)
B3: SW6.2, U1.28 (A11)
B4: SW9.2, U1.29 (A12)
B5: SW7.2, U1.30 (A15)
B6: SW2.2, U1.31 (B3)
B7: SW4.2, U1.32 (B4)
B8: SW8.2, U1.33 (B5)
B9: SW10.2, U1.34 (B6)
Buz: BZ1.1 (+), C1.1, U1.25 (A8)
GND: BT1.2 (-), BZ1.2 (-), C1.2, C2.2, C3.2, C4.2, C5.2, C6.2, C7.2, C8.2, C9.2, J1.1 (GND), LCD_Nokia1.8 (GND), R1.2, R2.2, R3.2, R4.2, R5.2, R6.2, R7.2, R8.2, R9.2, U1.19 (G), U1.20 (G), U1.39 (G), U2.1 (GND)
LCD_BL: LCD_Nokia1.7 (BL), U1.13 (B0)
LCD_CS: LCD_Nokia1.2 (CE), R11.1, U1.8 (A3)
LCD_DC: LCD_Nokia1.3 (DC), U1.6 (A1)
LCD_RST: LCD_Nokia1.1 (RST), U1.5 (A0)
MISO: J1.3 (MISO), U1.11 (A6)
MOSI: J1.4 (MOSI), LCD_Nokia1.4 (Din), U1.12 (A7)
unnamed: C3.1, C9.1, SW1.2 (B), U2.2 (VO)
unnamed: R7.1, SW4.2
unnamed: R8.1, SW10.2
unnamed: R9.1, SW8.2
unnamed: R4.1, SW7.2
unnamed: R5.1, SW6.2
unnamed: R6.1, SW2.2
unnamed: R1.1, SW3.2
unnamed: R2.1, SW5.2
unnamed: R3.1, SW9.2
SCK: J1.5 (SCK), LCD_Nokia1.5 (CLK), U1.10 (A5)
SD_CS: J1.6 (CS), R10.2, U1.9 (A4)
VCC: C2.1, C7.1, SW1.1 (A), U1.1 (VB)

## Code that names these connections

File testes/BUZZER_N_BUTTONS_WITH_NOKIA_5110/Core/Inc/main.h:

/* USER CODE BEGIN Header */
/**
  ******************************************************************************
  * @file           : main.h
  * @brief          : Header for main.c file.
  *                   This file contains the common defines of the application.
  ******************************************************************************
  * @attention
  *
  * Copyright (c) 2026 STMicroelectronics.
  * All rights reserved.
  *
  * This software is licensed under terms that can be found in the LICENSE file
  * in the root directory of this software component.
  * If no LICENSE file comes with this software, it is provided AS-IS.
  *
  ******************************************************************************
  */
/* USER CODE END Header */

/* Define to prevent recursive inclusion -------------------------------------*/
#ifndef __MAIN_H
#define __MAIN_H

#ifdef __cplusplus
extern "C" {
#endif

/* Includes ------------------------------------------------------------------*/
#include "stm32f1xx_hal.h"

/* Private includes ----------------------------------------------------------*/
/* USER CODE BEGIN Includes */

/* USER CODE END Includes */

/* Exported types ------------------------------------------------------------*/
/* USER CODE BEGIN ET */

/* USER CODE END ET */

/* Exported constants --------------------------------------------------------*/
/* USER CODE BEGIN EC */

/* USER CODE END EC */

/* Exported macro ------------------------------------------------------------*/
/* USER CODE BEGIN EM */

/* USER CODE END EM */

void HAL_TIM_MspPostInit(TIM_HandleTypeDef *htim);

/* Exported functions prototypes ---------------------------------------------*/
void Error_Handler(void);

/* USER CODE BEGIN EFP */

/* USER CODE END EFP */

/* Private defines -----------------------------------------------------------*/
#define LCD_RST_Pin GPIO_PIN_0
#define LCD_RST_GPIO_Port GPIOA
#define LCD_DC_Pin GPIO_PIN_1
#define LCD_DC_GPIO_Port GPIOA
#define LCD_CS_Pin GPIO_PIN_3
#define LCD_CS_GPIO_Port GPIOA
#define CS_SD_Pin GPIO_PIN_4
#define CS_SD_GPIO_Port GPIOA
#define SCK_Pin GPIO_PIN_5
#define SCK_GPIO_Port GPIOA
#define MISO_Pin GPIO_PIN_6
#define MISO_GPIO_Port GPIOA
#define MOSI_Pin GPIO_PIN_7
#define MOSI_GPIO_Port GPIOA
#define LCD_BL_Pin GPIO_PIN_0
#define LCD_BL_GPIO_Port GPIOB
#define BUZ_Pin GPIO_PIN_8
#define BUZ_GPIO_Port GPIOA
#define B1_Pin GPIO_PIN_9
#define B1_GPIO_Port GPIOA
#define B2_Pin GPIO_PIN_10
#define B2_GPIO_Port GPIOA
#define B3_Pin GPIO_PIN_11
#define B3_GPIO_Port GPIOA
#define B4_Pin GPIO_PIN_12
#define B4_GPIO_Port GPIOA
#define B5_Pin GPIO_PIN_15
#define B5_GPIO_Port GPIOA
#define B6_Pin GPIO_PIN_3
#define B6_GPIO_Port GPIOB
#define B7_Pin GPIO_PIN_4
#define B7_GPIO_Port GPIOB
#define B8_Pin GPIO_PIN_5
#define B8_GPIO_Port GPIOB
#define B9_Pin GPIO_PIN_6
#define B9_GPIO_Port GPIOB

/* USER CODE BEGIN Private defines */

/* USER CODE END Private defines */

#ifdef __cplusplus
}
#endif

#endif /* __MAIN_H */

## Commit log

2025-09-21 Criação de README.md
    Criação da pasta de hardware.
2025-09-21 Criação de README.md
    Criação da pasta de firmware.
2025-09-21 Criação de README.md
    Criação da pasta de documentação.
2025-09-21 Criação de README.md
    Criação da pasta de assets.
2025-09-21 Criação de README.md
    Criação da pasta de testes.
2025-12-19 Begin the schematic PCB project
2025-12-19 ADD SDCARD MODULE, LCD and Buzzer circuit and Power Supply circuit
2025-12-20 ADD a project ProtoGame in STM32F103C8T6 and set pinout
2025-12-20 Update schemmatic
2025-12-20 Update schematic
2025-12-26 Add MCU Pinout
2025-12-26 Add the footprints and 3D models for ProtoGame PCI and add the png assets v0
2026-01-17 ProtoGame v2 its complete and with new design, add assets images: footprint and 3d model
2026-01-19 Código do STM32
2026-01-19 add 'frufrus' in pcb
2026-01-19 add asset (pcb without mask image)
2026-01-19 Revise README for STM32 portable game documentation
    This update expands the README to include detailed documentation for a portable video game project using the STM32F103C8T6 microcontroller, covering objectives, system overview, component choices, an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
2026-01-20 add gerber and drill files to manufactoring PCB
2026-01-20 add assets images and replace vias and tracks in pcb, corrige the tracks and generate the gerber and drill files and generate the schematic pdf and generate the pcb in 3d and generatee the BoM
2026-01-20 Revise README for clarity and project details
    Updated the README to reflect changes in project details and structure, including improved section titles and descriptions for clarity.
2026-01-20 add assets and datasheets
2026-01-20 add image in assets
2026-01-20 Enhance README with component details and images
    Add detailed descriptions and images for components used in the project, including microcontroller, display, storage, input interface, and audio.
2026-01-20 Atualizar o README.md
2026-01-21 little bit refactor in schematic
2026-01-21 Add jobset files
2026-01-21 add image to assets
2026-01-21 Revise HARDWARE.md with new schematic links and images
    Updated schematic references and added PCB layer images.
2026-01-23 Add NOKIA-5110 firmware test
2026-01-23 Add 'GRC NELES' in NOKIA-5110 firmware test
2026-01-23 Initiate the firmware test
2026-01-24 modified and ajust
2026-01-24 asset image test LCD
2026-01-24 add image assets
2026-01-24 Expand documentation for STM32F103xx microcontrollers and fineshed
    Add detailed overview and features of STM32F103xx family.
2026-01-24 fineshed the README.md
2026-01-26 add more tests components
